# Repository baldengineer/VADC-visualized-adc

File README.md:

# VADC-visualized-adc
 Hardware project that shows how a SAR ADC works!

## Streaming notes
This project was created as a part of a [Bald Engineer Live Stream](https://twitch.tv/baldengineer). For stream-by-stream notes, [check out this repo](https://bald.ee/60-notes).

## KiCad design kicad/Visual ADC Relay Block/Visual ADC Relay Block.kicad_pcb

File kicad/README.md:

# Visualized ADC KiCad Design Files

## Visual ADC Relay Block
Single bit block of the DAC inside of the ADC. The board contains a relay, R resistor, 2R resistor, LEDs, a shift register, and a buffer. 

The shift register and buffer control the relay and six LEDs individually. The relay controls the 2R resistor. 

The idea is to daisy chain these together. (So far, only tested with 4 bits.)

Board was fabricated with OSH Park's 4 layer service. The fiberglass material helps the reverse-mount LEDs glow.

## Sample-Hold-Compare
These files are schematic-only. I captured the breadboard circuit we used for the sample-and-hold amplifier and op-amp as a comparator.

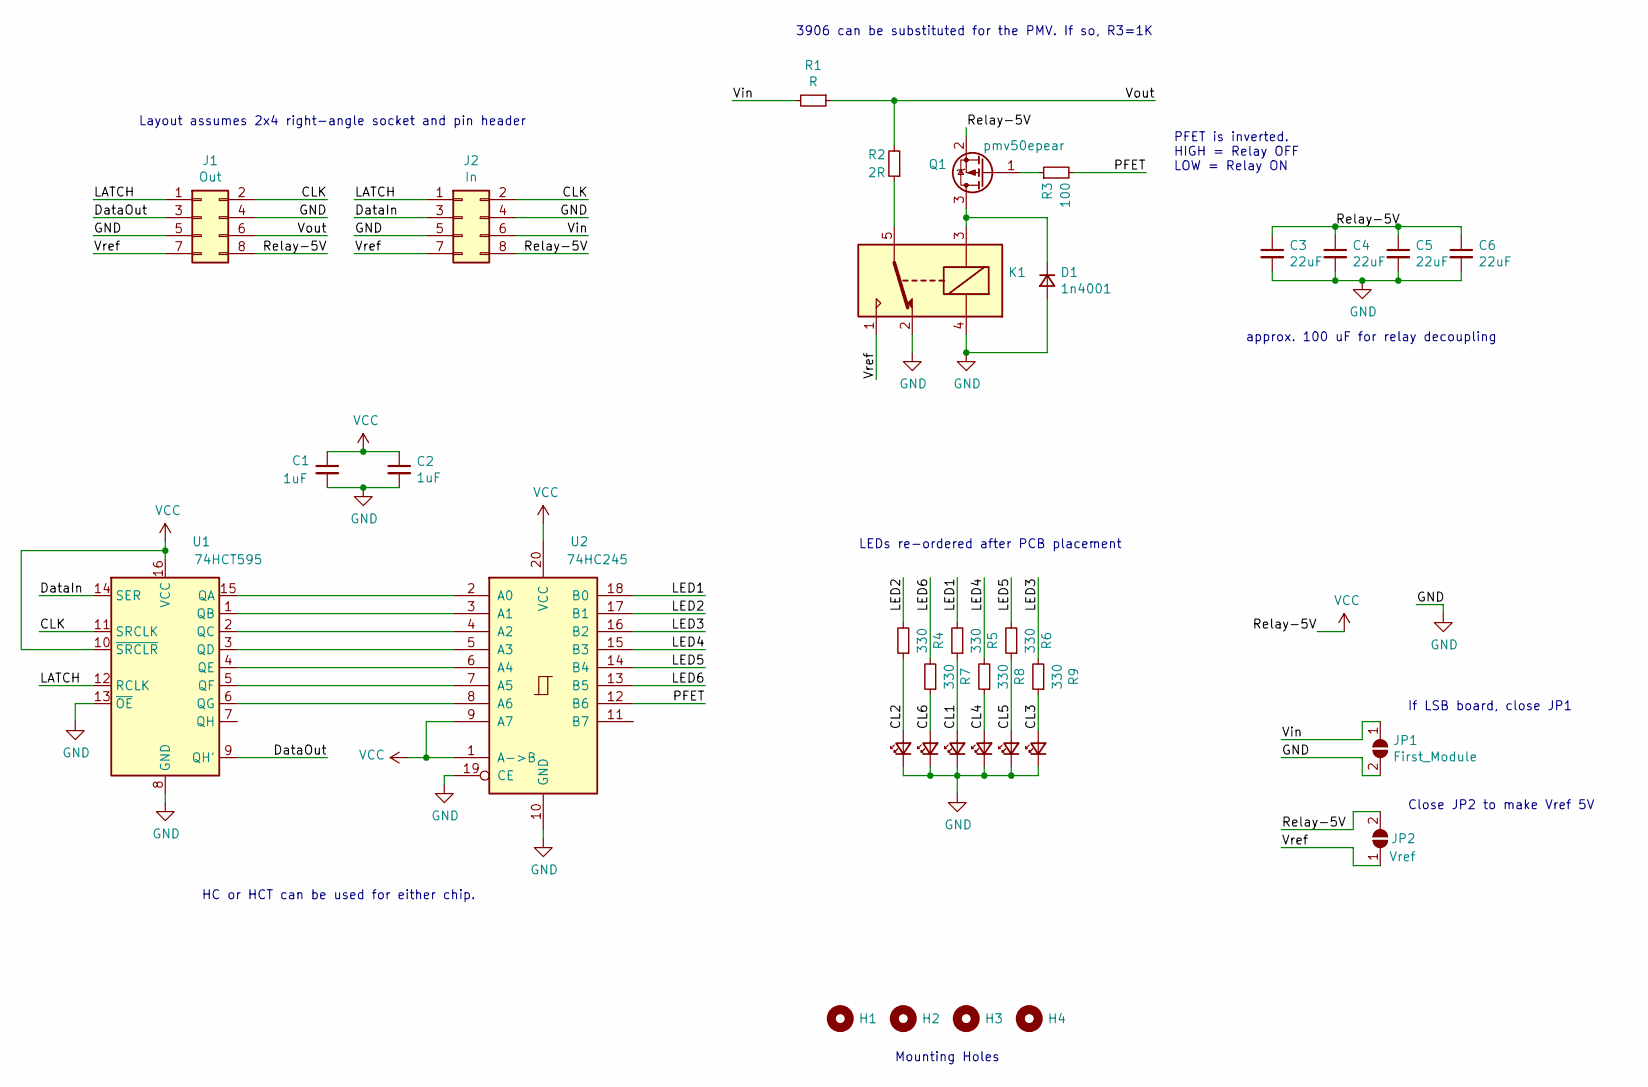
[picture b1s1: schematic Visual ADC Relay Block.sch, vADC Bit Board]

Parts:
C1, C2: 1uF; C_0805_2012Metric_Pad1.18x1.45mm_HandSolder
C3, C4, C5, C6: 22uF; C_0805_2012Metric_Pad1.18x1.45mm_HandSolder
D1: 1n4001; D_DO-41_SOD81_P10.16mm_Horizontal
D2, D3, D4, D5, D6, D7: LED_Small; LED_1206_3216Metric_ReverseMount_Hole1.8x2.4mm
H1, H2, H3, H4: MountingHole; MountingHole_2.7mm
J1: Out; PinHeader_2x04_P2.54mm_Vertical
J2: In; PinHeader_2x04_P2.54mm_Vertical
JP1: First_Module; SolderJumper-2_P1.3mm_Open_TrianglePad1.0x1.5mm
JP2: Vref; SolderJumper-2_P1.3mm_Open_TrianglePad1.0x1.5mm
K1: DIPxx-1Cxx-51x; Relay_SPDT_HsinDa_Y14
Q1: pmv50epear; SOT-23
R1: R; R_Axial_DIN0207_L6.3mm_D2.5mm_P10.16mm_Horizontal
R2: 2R; R_Axial_DIN0207_L6.3mm_D2.5mm_P10.16mm_Horizontal
R3: 100; R_0805_2012Metric_Pad1.20x1.40mm_HandSolder
R4, R5, R6, R7, R8, R9: 330; R_0805_2012Metric_Pad1.20x1.40mm_HandSolder
U1: 74HCT595; SO-16_3.9x9.9mm_P1.27mm
U2: 74HC245; SOIC-20W_7.5x12.8mm_P1.27mm

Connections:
/CL1: D3.2 (A), R5.1
/CL2: D4.2 (A), R4.1
/CL3: D5.2 (A), R9.1
/CL4: D6.2 (A), R8.1
/CL5: D7.2 (A), R6.1
/CL6: D2.2 (A), R7.1
/CLK: J1.2, J2.2, U1.11 (SRCLK)
/DataIn: J2.3, U1.14 (SER)
/DataOut: J1.3, U1.9 (QH')
/LATCH: J1.1, J2.1, U1.12 (RCLK)
/LED1: R5.2, U2.18 (B0)
/LED2: R4.2, U2.17 (B1)
/LED3: R9.2, U2.16 (B2)
/LED4: R8.2, U2.15 (B3)
/LED5: R6.2, U2.14 (B4)
/LED6: R7.2, U2.13 (B5)
/PFET: R3.2, U2.12 (B6)
/Vin: J2.6, JP1.1 (A), R1.2
/Vout: J1.6, R1.1, R2.2
/Vref: J1.7, J2.7, JP2.1 (A), K1.1
GND: C1.2, C2.2, C3.2, C4.2, C5.2, C6.2, D1.2 (A), D2.1 (K), D3.1 (K), D4.1 (K), D5.1 (K), D6.1 (K), D7.1 (K), J1.4, J1.5, J2.4, J2.5, JP1.2 (B), K1.2, K1.4, U1.8 (GND), U1.13 (~OE), U2.10 (GND), U2.19 (CE)
unnamed: D1.1 (K), K1.3, Q1.3 (D)
unnamed: K1.5, K1.6, R2.1
unnamed: Q1.1 (G), R3.1
unnamed: U1.1 (QB), U2.3 (A1)
unnamed: U1.2 (QC), U2.4 (A2)
unnamed: U1.3 (QD), U2.5 (A3)
unnamed: U1.4 (QE), U2.6 (A4)
unnamed: U1.5 (QF), U2.7 (A5)
unnamed: U1.6 (QG), U2.8 (A6)
unnamed: U1.15 (QA), U2.2 (A0)
VCC: C1.1, C2.1, C3.1, C4.1, C5.1, C6.1, J1.8, J2.8, JP2.2 (B), Q1.2 (S), U1.10 (~SRCLR), U1.16 (VCC), U2.1 (A->B), U2.9 (A7), U2.20 (VCC)

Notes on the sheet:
3906 can be substituted for the PMV. If so, R3=1K
If LSB board, close JP1
Close JP2 to make Vref 5V
LEDs re-ordered after PCB placement
PFET is inverted. HIGH = Relay OFF LOW = Relay ON
approx. 100 uF for relay decoupling
Layout assumes 2x4 right-angle socket and pin header
HC or HCT can be used for either chip.
Mounting Holes

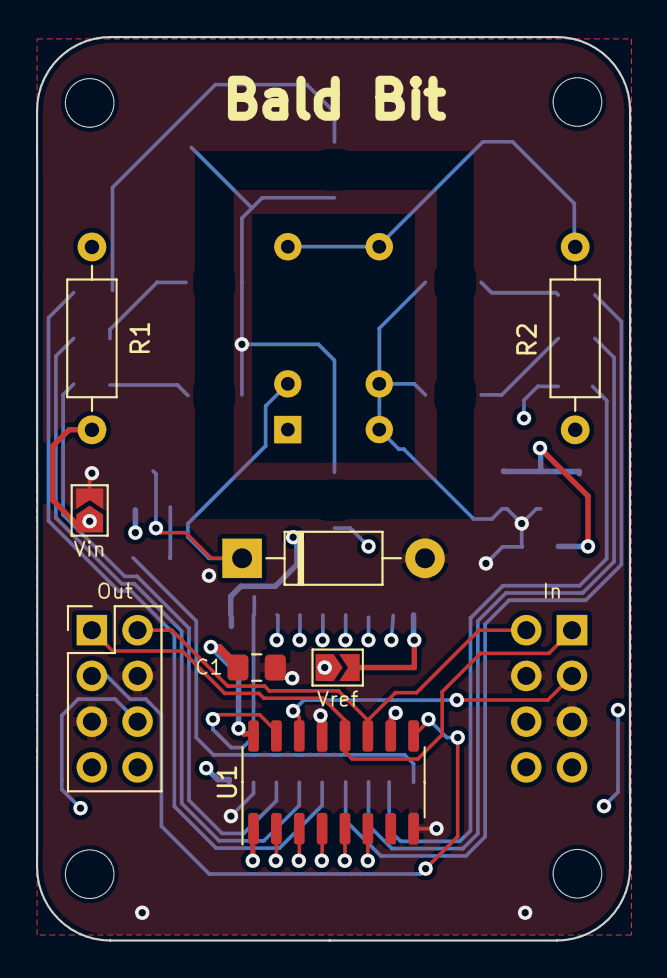
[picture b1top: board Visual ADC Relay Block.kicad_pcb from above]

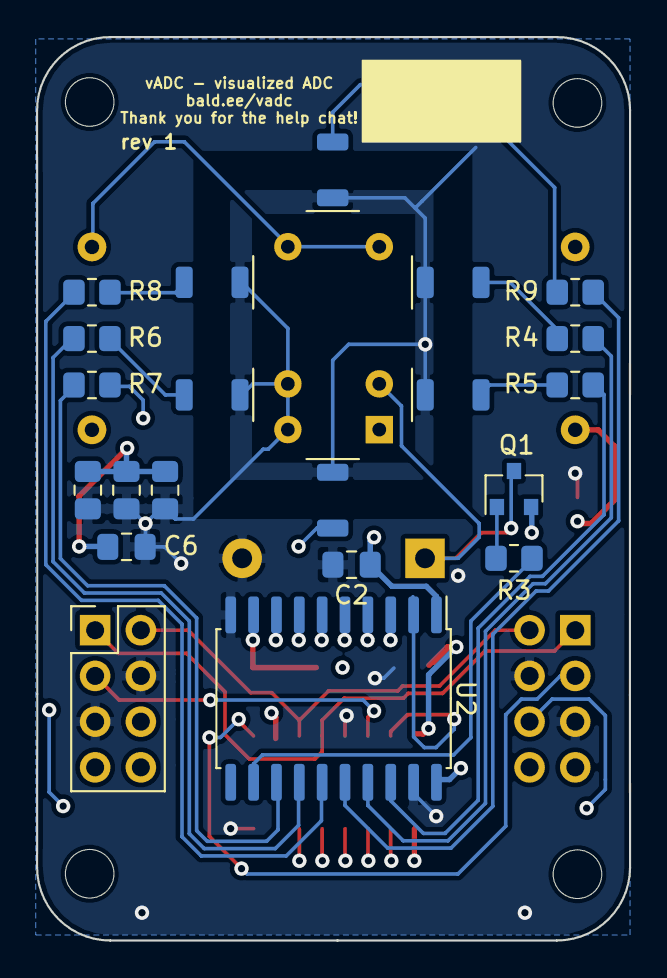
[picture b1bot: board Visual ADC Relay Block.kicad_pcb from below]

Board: 4 copper layers, 32.9 x 50.2 mm, 34 parts (21 on the bottom side), 32 nets.

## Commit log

2021-02-11 Initial Create
2021-02-11 V1 kicad layout
    going to re-work and add shift registers....
2021-02-11 before changing to ribbons
2021-02-11 time to clean up
2021-02-11 why won't you stop
2021-02-11 Passed DRC and No Rats
2021-02-11 Silk clean up
2021-02-14 change in/out but need to save brains
2021-02-14 pass DRC yay!
2021-02-14 relay masks done
    outline around relay area with no copper or mask on any layer
2021-02-14 added probe gnd now silky time
2021-02-14 rev1 pre-submit
    haven't submitted rev to board house yet
2021-02-28 rev1 boards tested
2021-03-01 initial DAC code
    converted spaghetti code from stream into a more manageable project, to drive the DAC.
2021-03-01 KiCad Notes and Clean-up
    Finalized a few details on the schematic. Also created notes for each block based on experience building the boards.
2021-03-03 create readme for KiCad files
2021-03-03 added header image
2021-03-06 stream 21-03-05
2021-03-06 all the debug
2021-03-06 wait, it works?
2021-03-07 added tft
2021-03-11 what the what
    erroring out with: relocation truncated to fit: R_AVR_7_PCREL against `no symbol'
2021-03-11 post-stream clean-up (untested)
    cleaned up some potential problems based on the stream 3/10, still need to test.
2021-03-12 cal and bug fixes
    Fixed a bug with the step-by-step mode. Added external reference for the ADC (tied to regulator output), added range/two-line output when conversion is complete.
2021-03-14 bug fixes
    changed DAC voltage display code to use global variable. hardware wise, added heat sink to LM7805. It was having trouble regulating voltage.
2021-03-15 added moar blinky
    When a bit is being tested during the binary search, its LEDs now blink.
    The screen readout is now 2 lines during the search. First line is current DAC voltage and the second line is the binary code so far with ?, X, 0, and 1 indicators.
